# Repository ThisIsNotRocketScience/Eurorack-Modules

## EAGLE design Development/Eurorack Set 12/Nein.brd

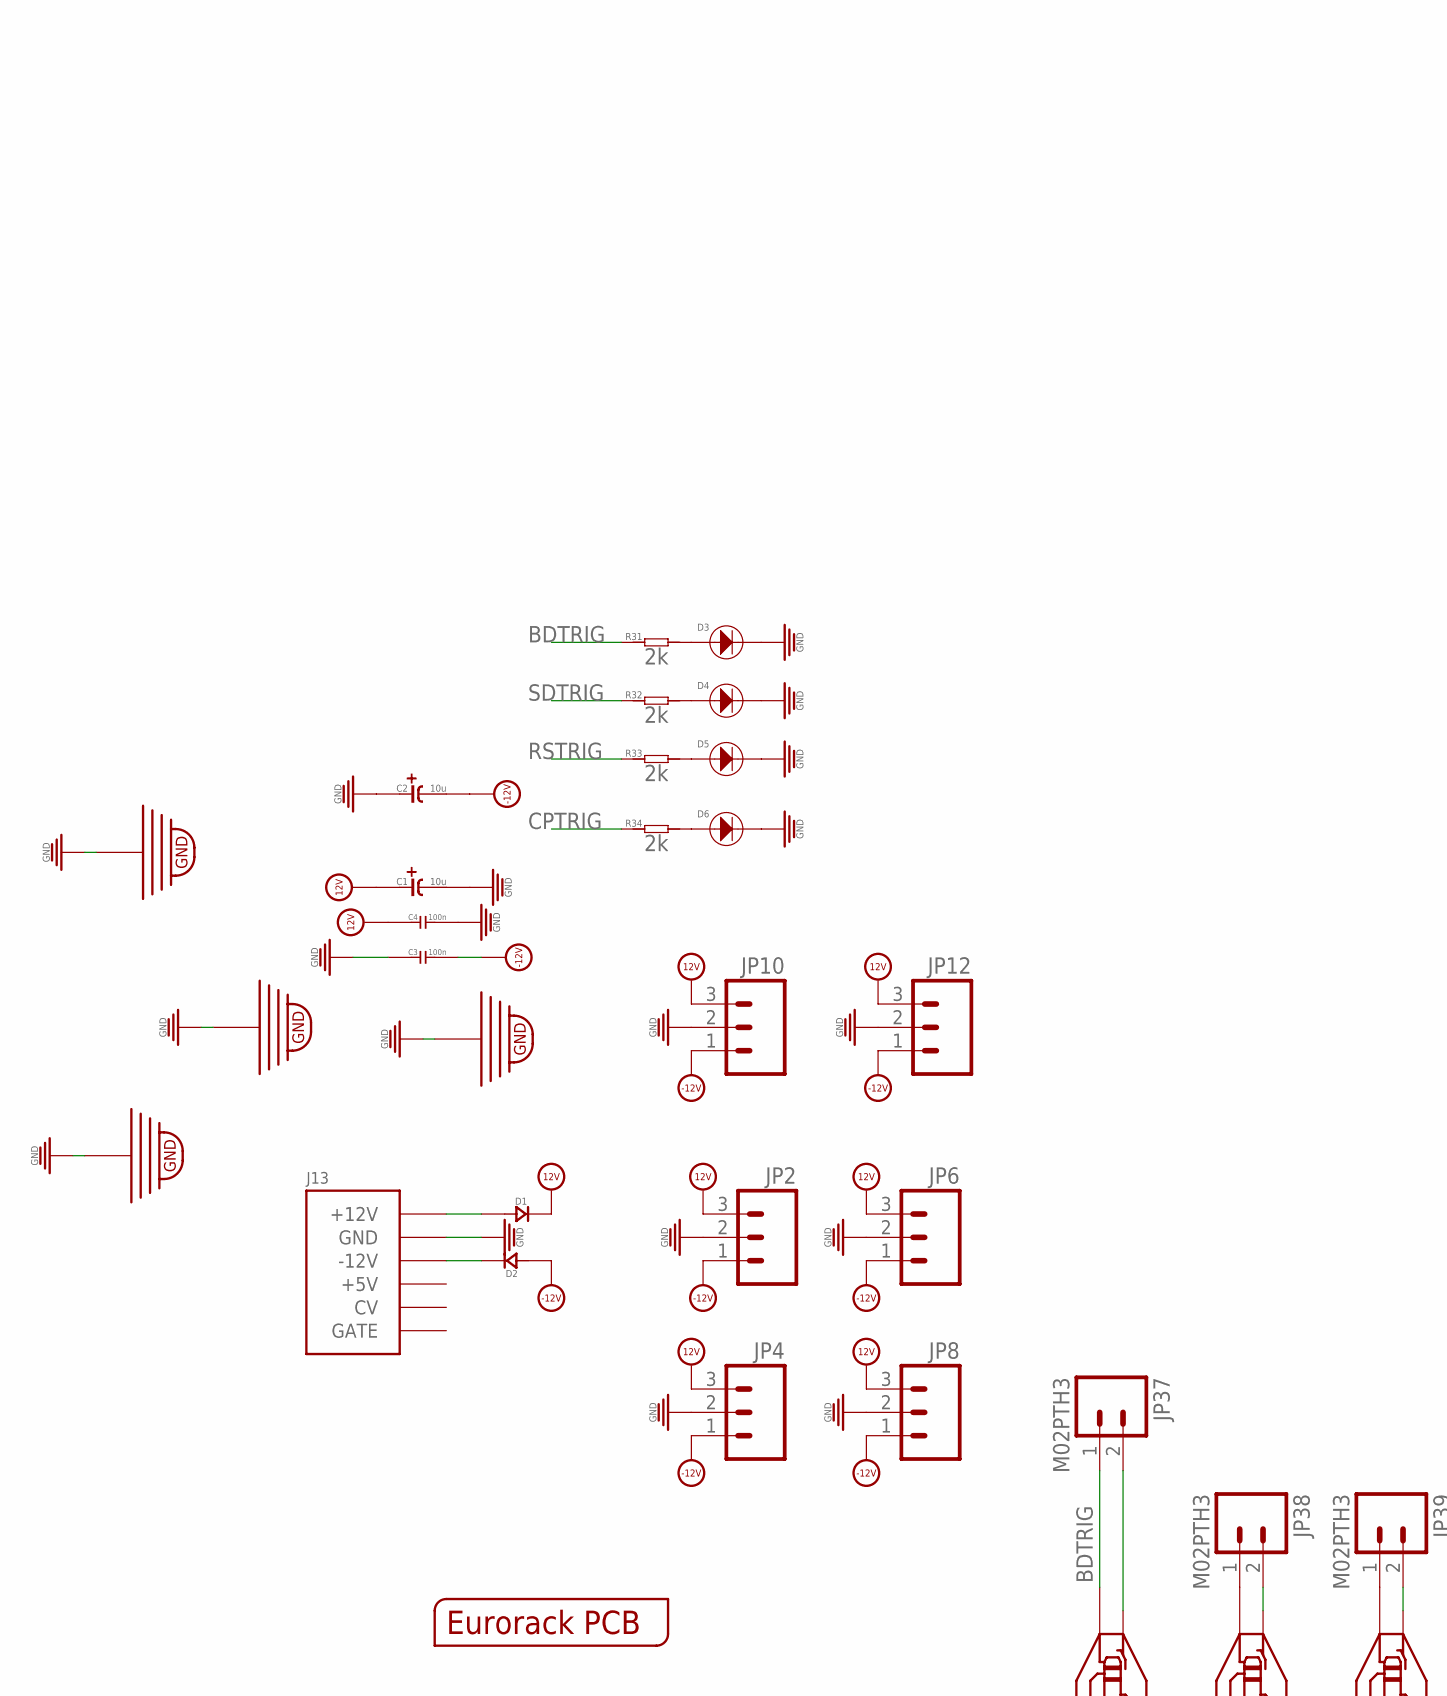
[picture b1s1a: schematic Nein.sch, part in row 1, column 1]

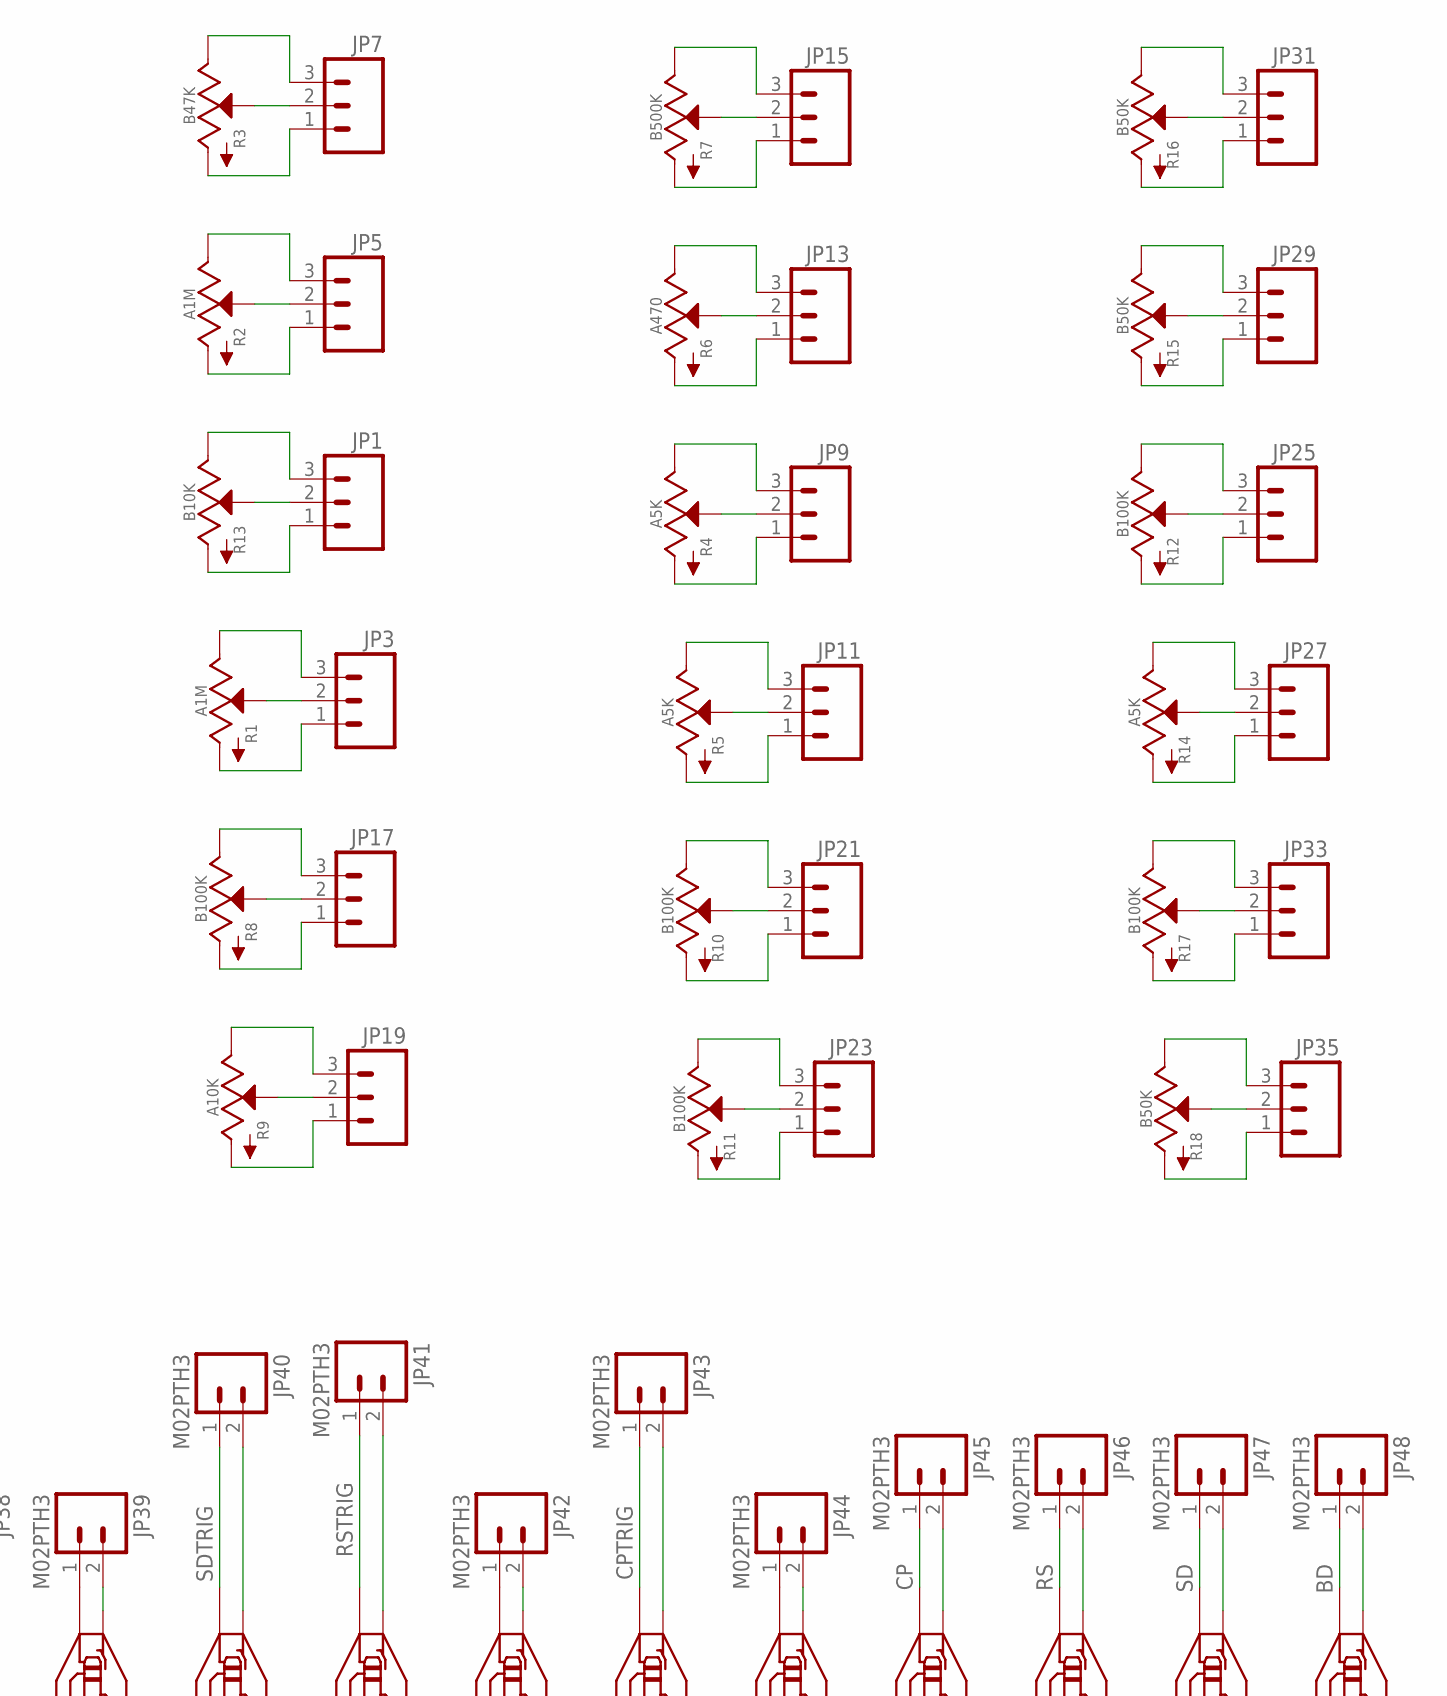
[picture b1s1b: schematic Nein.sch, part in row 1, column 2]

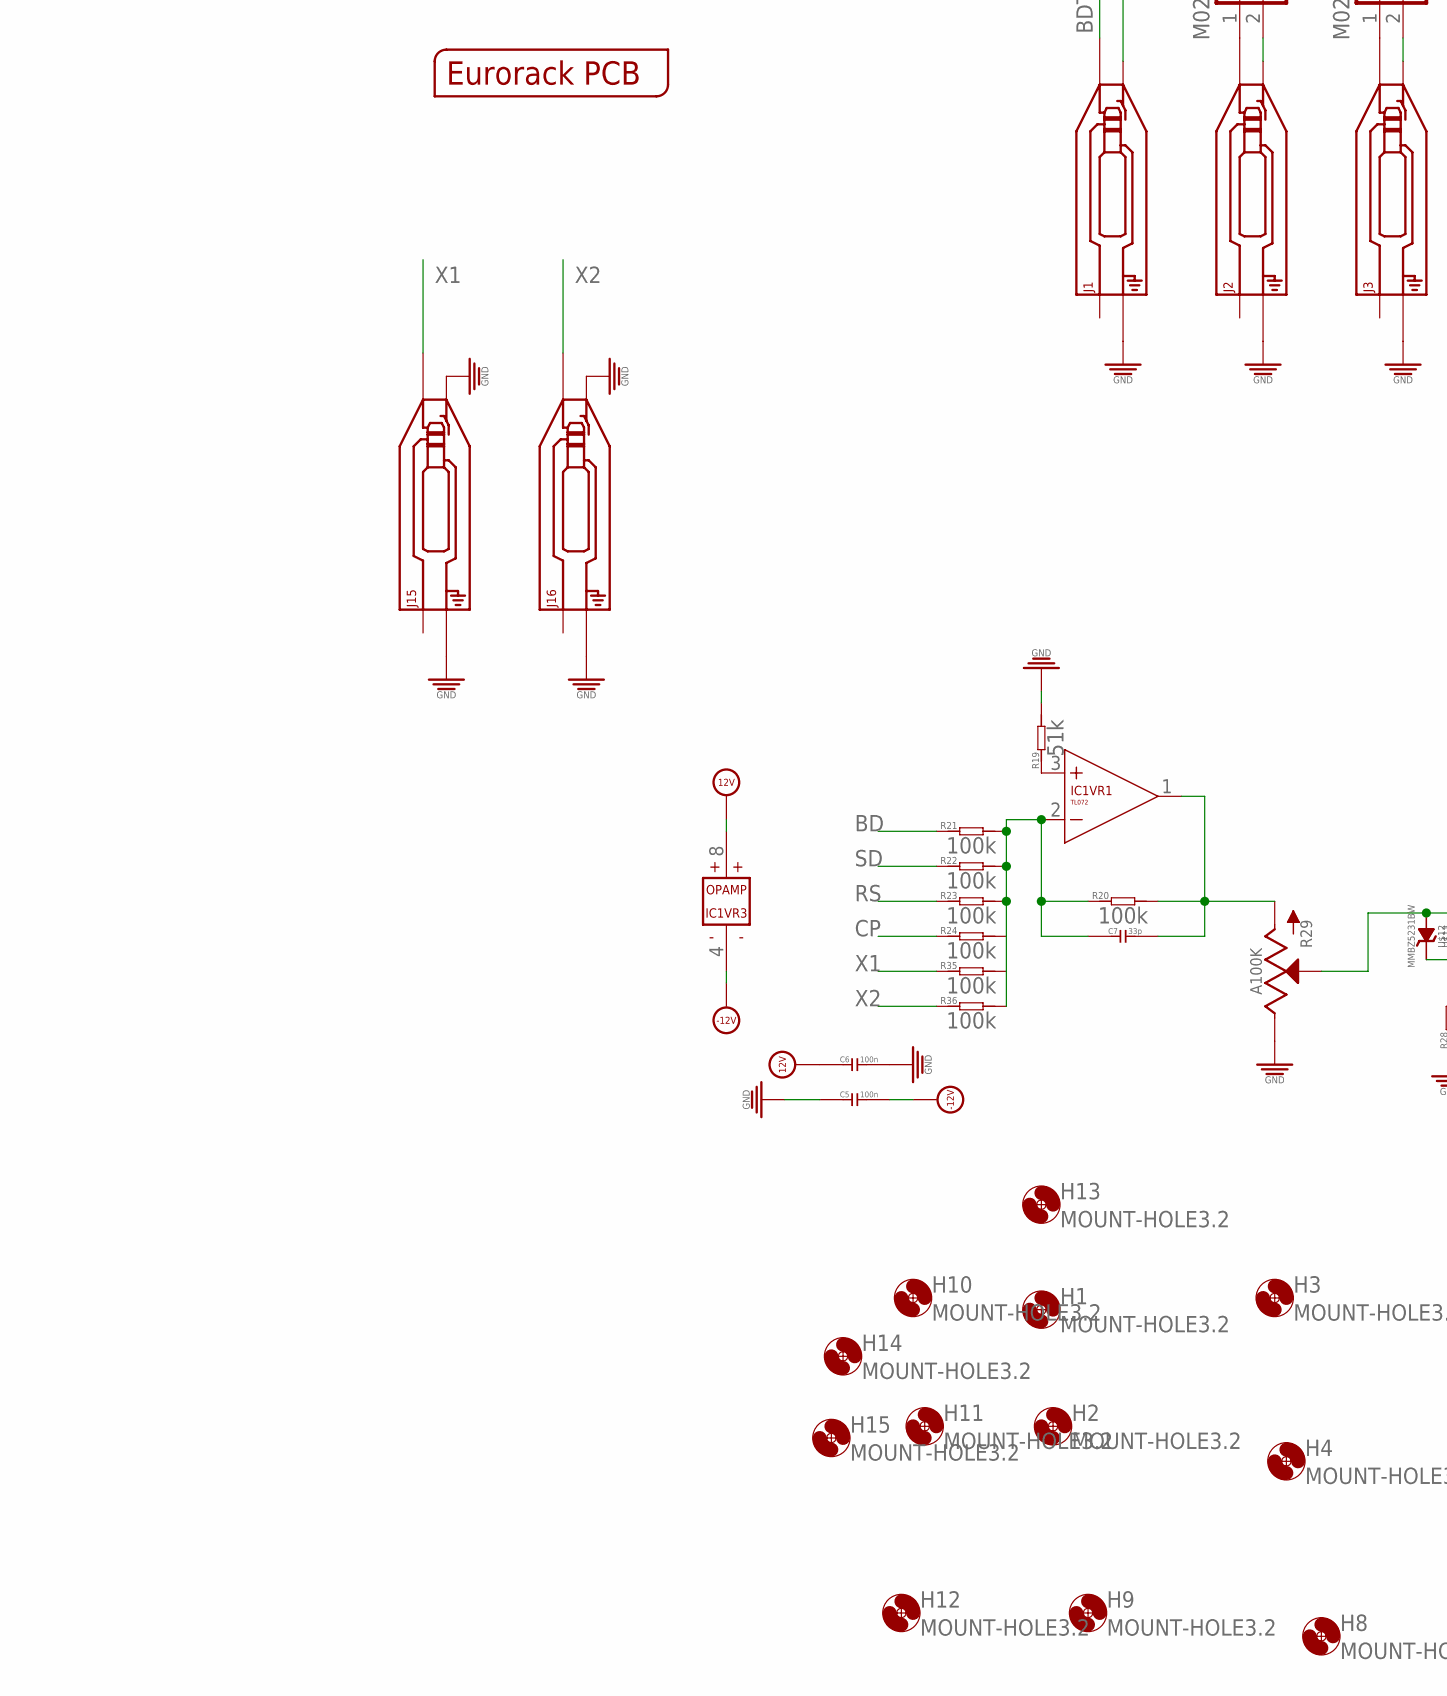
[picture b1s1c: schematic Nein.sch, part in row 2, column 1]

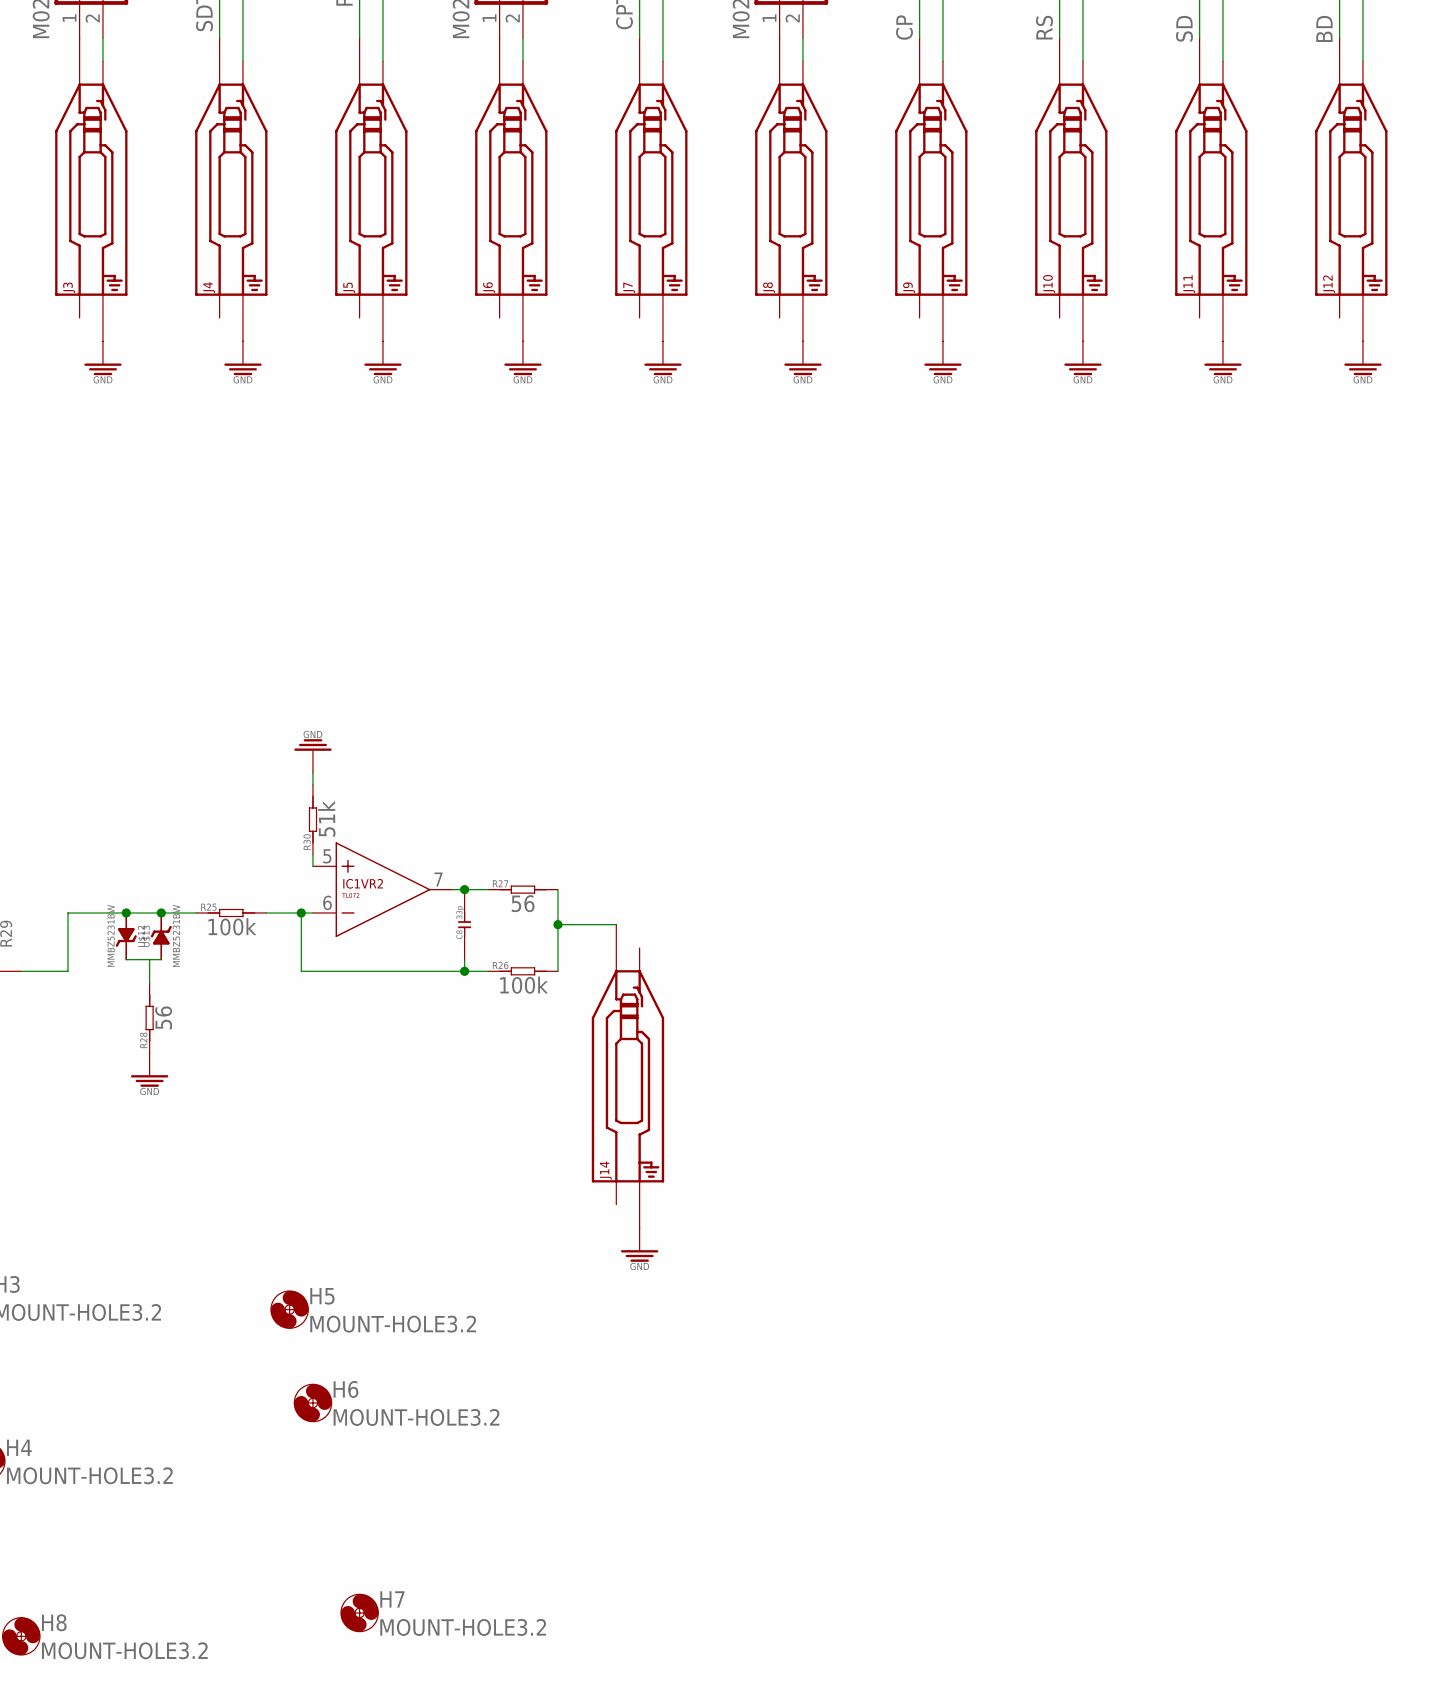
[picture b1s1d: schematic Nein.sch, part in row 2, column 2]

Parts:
C1, C2: 10u; CASE-A_3216
C3, C4, C5, C6: 100n; C0603
C7, C8: 33p; C0603
D1, D2: D-SMA; DO-214AC
D3, D4, D5, D6: LED3MM; 3MMLED
H1, H2, H3, H4, H5, H6, H7, H8, H9, H10, H11, H12, H13, H14, H15: MOUNT-HOLE3.2; 3,2
IC1: TL072; SO08
J1, J2, J3, J4, J5, J6, J7, J8, J9, J10, J11, J12, J14, J15, J16: AUDIO-JACK_SMALLSYMBOLNODRILL; 3.5MM-JACK-SWITCH-13MM-NOHOLES
J13: POWERSHROUDED; POWER_16_SHROUDED
JP1, JP2, JP3, JP4, JP5, JP6, JP7, JP8, JP9, JP10, JP11, JP12, JP13, JP15, JP17, JP19, JP21, JP23, JP25, JP27, JP29, JP31, JP33, JP35: M03LONGPADS; 1X03_LONGPADS
JP37, JP38, JP39, JP40, JP41, JP42, JP43, JP44, JP45, JP46, JP47, JP48: M02PTH3; 1X02_LONGPADS
PCB1: EURORACK_PCB36HP_10CM; EURORACK36HP
R1, R2: A1M; ALPS_POT_SQUAREHOLES
R3: B47K; ALPS_POT_SQUAREHOLES
R4, R5, R14: A5K; ALPS_POT_SQUAREHOLES
R6: A470; ALPS_POT_SQUAREHOLES
R7: B500K; ALPS_POT_SQUAREHOLES
R8, R10, R11, R12, R17: B100K; ALPS_POT_SQUAREHOLES
R9: A10K; ALPS_POT_SQUAREHOLES
R13: B10K; ALPS_POT_SQUAREHOLES
R15, R16, R18: B50K; ALPS_POT_SQUAREHOLES
R19, R30: 51k; R0603
R20, R21, R22, R23, R24, R25, R26, R35, R36: 100k; R0603
R27, R28: 56; R0603
R29: A100K; ALPS_POT_SQUAREHOLES
R31, R32, R33, R34: 2k; R0603
U$4, U$26, U$27, U$28: GNDLOOP; GROUNDLOOP
U$12, U$13: MMBZ5231BW; SOT-323-ZENER

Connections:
12V: C1.+ (1), C4.1, C6.1, D1.2 (-), IC1.8 (V+), JP2.3, JP4.3, JP6.3, JP8.3, JP10.3, JP12.3
-12V: C2.- (2), C3.2, C5.2, D2.1 (+), IC1.4 (V-), JP2.1, JP4.1, JP6.1, JP8.1, JP10.1, JP12.1
BD: J12.TIP_B@1 (TIP), J12.TIP_T@3 (TIP), JP48.1, R21.1
BDTRIG: J1.TIP_B@1 (TIP), J1.TIP_T@3 (TIP), JP37.1, R31.1
CP: J9.TIP_B@1 (TIP), J9.TIP_T@3 (TIP), JP45.1, R24.1
CPTRIG: J7.TIP_B@1 (TIP), J7.TIP_T@3 (TIP), JP43.1, R34.1
GND: C1.- (2), C2.+ (1), C3.1, C4.2, C5.1, C6.2, D3.-, D4.-, D5.-, D6.-, J1.RING_B@1 (RING), J1.RING_T@3 (RING), J2.RING_B@1 (RING), J2.RING_T@3 (RING), J3.RING_B@1 (RING), J3.RING_T@3 (RING), J4.RING_B@1 (RING), J4.RING_T@3 (RING), J5.RING_B@1 (RING), J5.RING_T@3 (RING), J6.RING_B@1 (RING), J6.RING_T@3 (RING), J7.RING_B@1 (RING), J7.RING_T@3 (RING), J8.RING_B@1 (RING), J8.RING_T@3 (RING), J9.RING_B@1 (RING), J9.RING_T@3 (RING), J10.RING_B@1 (RING), J10.RING_T@3 (RING), J11.RING_B@1 (RING), J11.RING_T@3 (RING), J12.RING_B@1 (RING), J12.RING_T@3 (RING), J13.3 (GND), J13.4 (GND), J13.5 (GND), J13.6 (GND), J13.7 (GND), J13.8 (GND), J14.RING_B@1 (RING), J14.RING_T@3 (RING), J15.RING_B@1 (RING), J15.RING_T@3 (RING), J15.SWITCH_B@1 (SWITCH), J15.SWITCH_T@3 (SWITCH), J16.RING_B@1 (RING), J16.RING_T@3 (RING), J16.SWITCH_B@1 (SWITCH), J16.SWITCH_T@3 (SWITCH), JP2.2, JP4.2, JP6.2, JP8.2, JP10.2, JP12.2, R19.2, R28.1, R29.P$1 (E), R30.2, U$4.P$1, U$4.P$2, U$26.P$1, U$26.P$2, U$27.P$1, U$27.P$2, U$28.P$1, U$28.P$2
unnamed: D1.1 (+), J13.9 (+12V), J13.10 (+12V)
unnamed: D2.2 (-), J13.1 (-12V), J13.2 (-12V)
unnamed: JP1.2, R13.P$2 (S)
unnamed: JP1.3, R13.P$1 (E)
unnamed: JP1.1, R13.P$3 (A)
unnamed: JP3.2, R1.P$2 (S)
unnamed: JP3.3, R1.P$1 (E)
unnamed: JP3.1, R1.P$3 (A)
unnamed: JP5.2, R2.P$2 (S)
unnamed: JP5.3, R2.P$1 (E)
unnamed: JP5.1, R2.P$3 (A)
unnamed: JP7.2, R3.P$2 (S)
unnamed: JP7.3, R3.P$1 (E)
unnamed: JP7.1, R3.P$3 (A)
unnamed: JP9.2, R4.P$2 (S)
unnamed: JP9.3, R4.P$1 (E)
unnamed: JP9.1, R4.P$3 (A)
unnamed: JP11.2, R5.P$2 (S)
unnamed: JP11.3, R5.P$1 (E)
unnamed: JP11.1, R5.P$3 (A)
unnamed: JP13.2, R6.P$2 (S)
unnamed: JP13.3, R6.P$1 (E)
unnamed: JP13.1, R6.P$3 (A)
unnamed: JP15.2, R7.P$2 (S)
unnamed: JP15.3, R7.P$1 (E)
unnamed: JP15.1, R7.P$3 (A)
unnamed: JP17.2, R8.P$2 (S)
unnamed: JP17.3, R8.P$1 (E)
unnamed: JP17.1, R8.P$3 (A)
unnamed: JP19.2, R9.P$2 (S)
unnamed: JP19.3, R9.P$1 (E)
unnamed: JP19.1, R9.P$3 (A)
unnamed: JP21.2, R10.P$2 (S)
unnamed: JP21.3, R10.P$1 (E)
unnamed: JP21.1, R10.P$3 (A)
unnamed: JP23.2, R11.P$2 (S)
unnamed: JP23.3, R11.P$1 (E)
unnamed: JP23.1, R11.P$3 (A)
unnamed: JP25.2, R12.P$2 (S)
unnamed: JP25.3, R12.P$1 (E)
unnamed: JP25.1, R12.P$3 (A)
unnamed: JP27.2, R14.P$2 (S)
unnamed: JP27.3, R14.P$1 (E)
unnamed: JP27.1, R14.P$3 (A)
unnamed: JP29.2, R15.P$2 (S)
unnamed: JP29.3, R15.P$1 (E)
unnamed: JP29.1, R15.P$3 (A)
unnamed: JP31.2, R16.P$2 (S)
unnamed: JP31.3, R16.P$1 (E)
unnamed: JP31.1, R16.P$3 (A)
unnamed: JP33.2, R17.P$2 (S)
unnamed: JP33.3, R17.P$1 (E)
unnamed: JP33.1, R17.P$3 (A)
unnamed: JP35.2, R18.P$2 (S)
unnamed: JP35.3, R18.P$1 (E)
unnamed: JP35.1, R18.P$3 (A)
unnamed: J1.SWITCH_B@1 (SWITCH), J1.SWITCH_T@3 (SWITCH), JP37.2
unnamed: J2.TIP_B@1 (TIP), J2.TIP_T@3 (TIP), JP38.1
unnamed: J2.SWITCH_B@1 (SWITCH), J2.SWITCH_T@3 (SWITCH), JP38.2
unnamed: J3.TIP_B@1 (TIP), J3.TIP_T@3 (TIP), JP39.1
unnamed: J3.SWITCH_B@1 (SWITCH), J3.SWITCH_T@3 (SWITCH), JP39.2
unnamed: J4.SWITCH_B@1 (SWITCH), J4.SWITCH_T@3 (SWITCH), JP40.2
unnamed: J5.SWITCH_B@1 (SWITCH), J5.SWITCH_T@3 (SWITCH), JP41.2
unnamed: J6.TIP_B@1 (TIP), J6.TIP_T@3 (TIP), JP42.1
unnamed: J6.SWITCH_B@1 (SWITCH), J6.SWITCH_T@3 (SWITCH), JP42.2
unnamed: J7.SWITCH_B@1 (SWITCH), J7.SWITCH_T@3 (SWITCH), JP43.2
unnamed: J8.TIP_B@1 (TIP), J8.TIP_T@3 (TIP), JP44.1
unnamed: J8.SWITCH_B@1 (SWITCH), J8.SWITCH_T@3 (SWITCH), JP44.2
unnamed: IC1.3 (+IN), R19.1
unnamed: J9.SWITCH_B@1 (SWITCH), J9.SWITCH_T@3 (SWITCH), JP45.2
unnamed: IC1.5 (+IN), R30.1
unnamed: J10.SWITCH_B@1 (SWITCH), J10.SWITCH_T@3 (SWITCH), JP46.2
unnamed: D3.+, R31.2
unnamed: J11.SWITCH_B@1 (SWITCH), J11.SWITCH_T@3 (SWITCH), JP47.2
unnamed: D4.+, R32.2
unnamed: J12.SWITCH_B@1 (SWITCH), J12.SWITCH_T@3 (SWITCH), JP48.2
unnamed: D5.+, R33.2
unnamed: D6.+, R34.2
unnamed: C7.1, IC1.2 (-IN), R20.1, R21.2, R22.2, R23.2, R24.2, R35.2, R36.2
unnamed: R28.2, U$12.CATHODE, U$13.ANODE
unnamed: C7.2, IC1.1 (OUT), R20.2, R29.P$3 (A)
unnamed: C8.1, IC1.6 (-IN), R25.2, R26.1
unnamed: C8.2, IC1.7 (OUT), R27.1
unnamed: J14.TIP_B@1 (TIP), J14.TIP_T@3 (TIP), R26.2, R27.2
unnamed: R25.1, R29.P$2 (S), U$12.ANODE, U$13.CATHODE
RS: J10.TIP_B@1 (TIP), J10.TIP_T@3 (TIP), JP46.1, R23.1
RSTRIG: J5.TIP_B@1 (TIP), J5.TIP_T@3 (TIP), JP41.1, R33.1
SD: J11.TIP_B@1 (TIP), J11.TIP_T@3 (TIP), JP47.1, R22.1
SDTRIG: J4.TIP_B@1 (TIP), J4.TIP_T@3 (TIP), JP40.1, R32.1
X1: J15.TIP_B@1 (TIP), J15.TIP_T@3 (TIP), R35.1
X2: J16.TIP_B@1 (TIP), J16.TIP_T@3 (TIP), R36.1

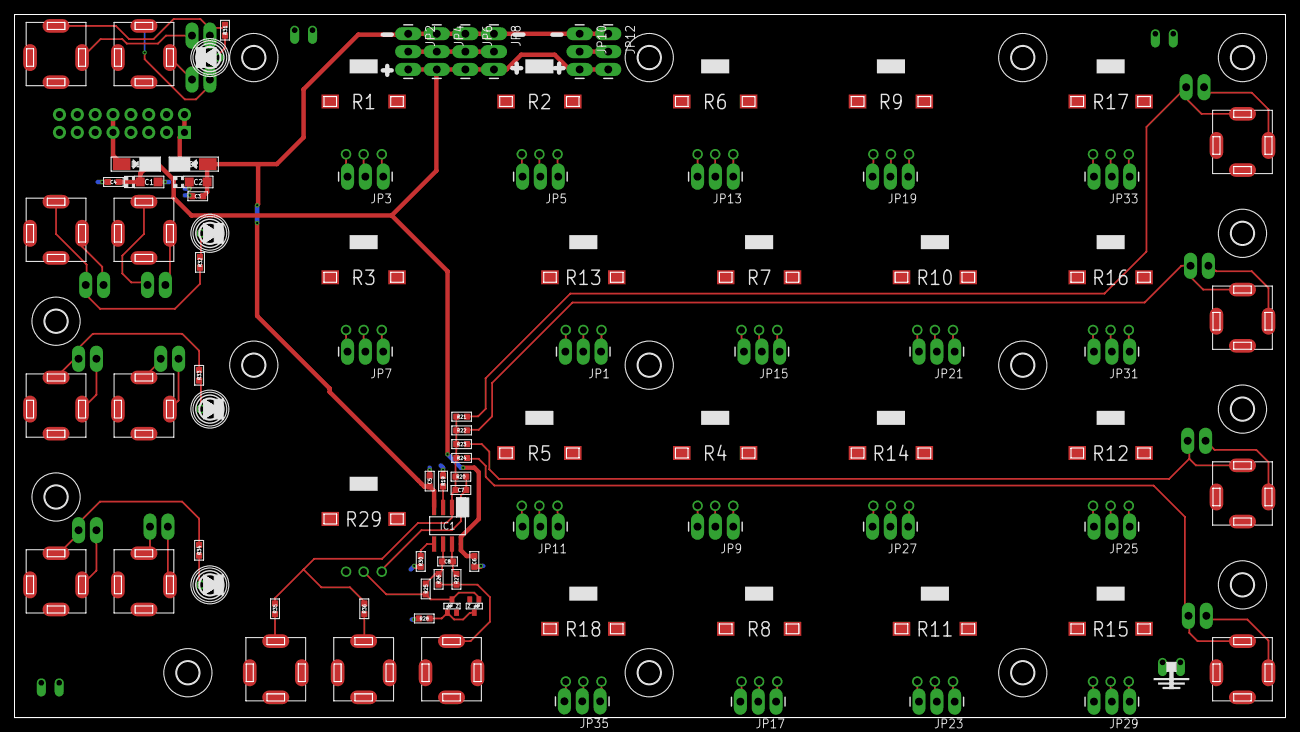
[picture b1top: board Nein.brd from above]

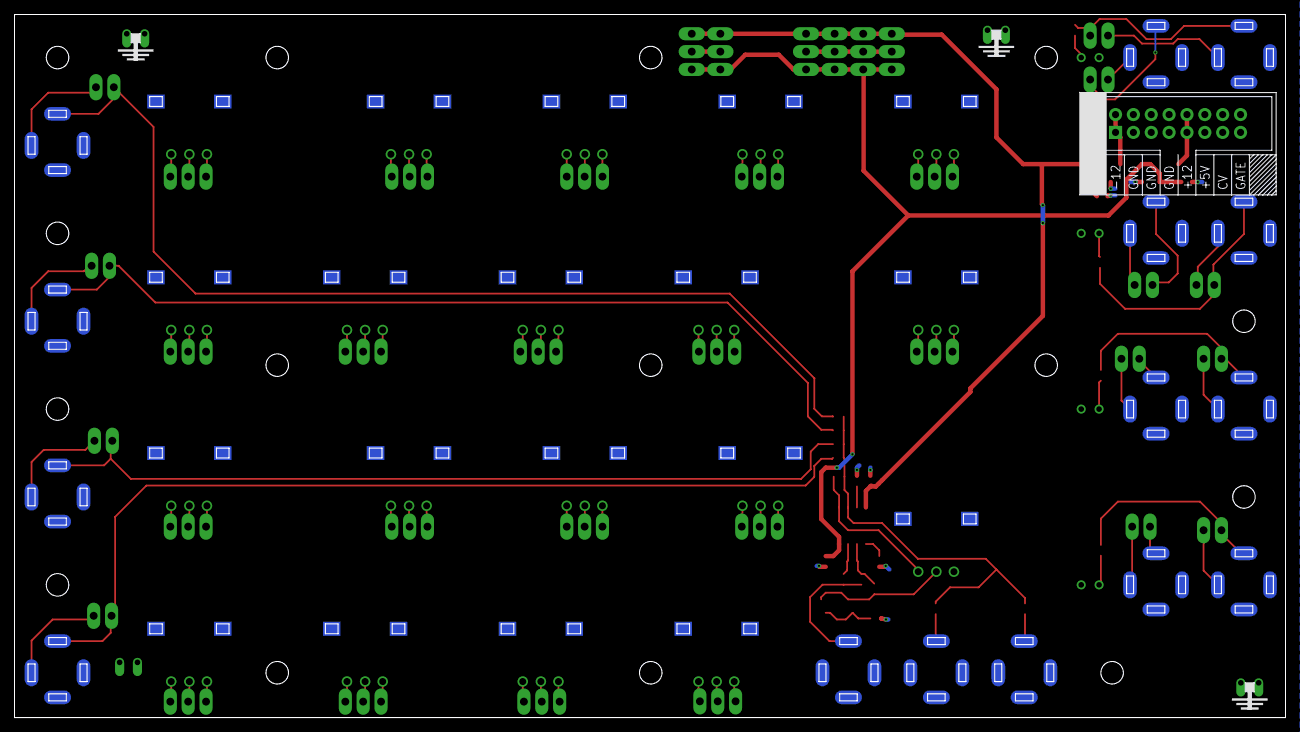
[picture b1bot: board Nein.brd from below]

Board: 2 copper layers, 180.8 x 100.0 mm, 125 parts (4 on the bottom side), 98 nets.

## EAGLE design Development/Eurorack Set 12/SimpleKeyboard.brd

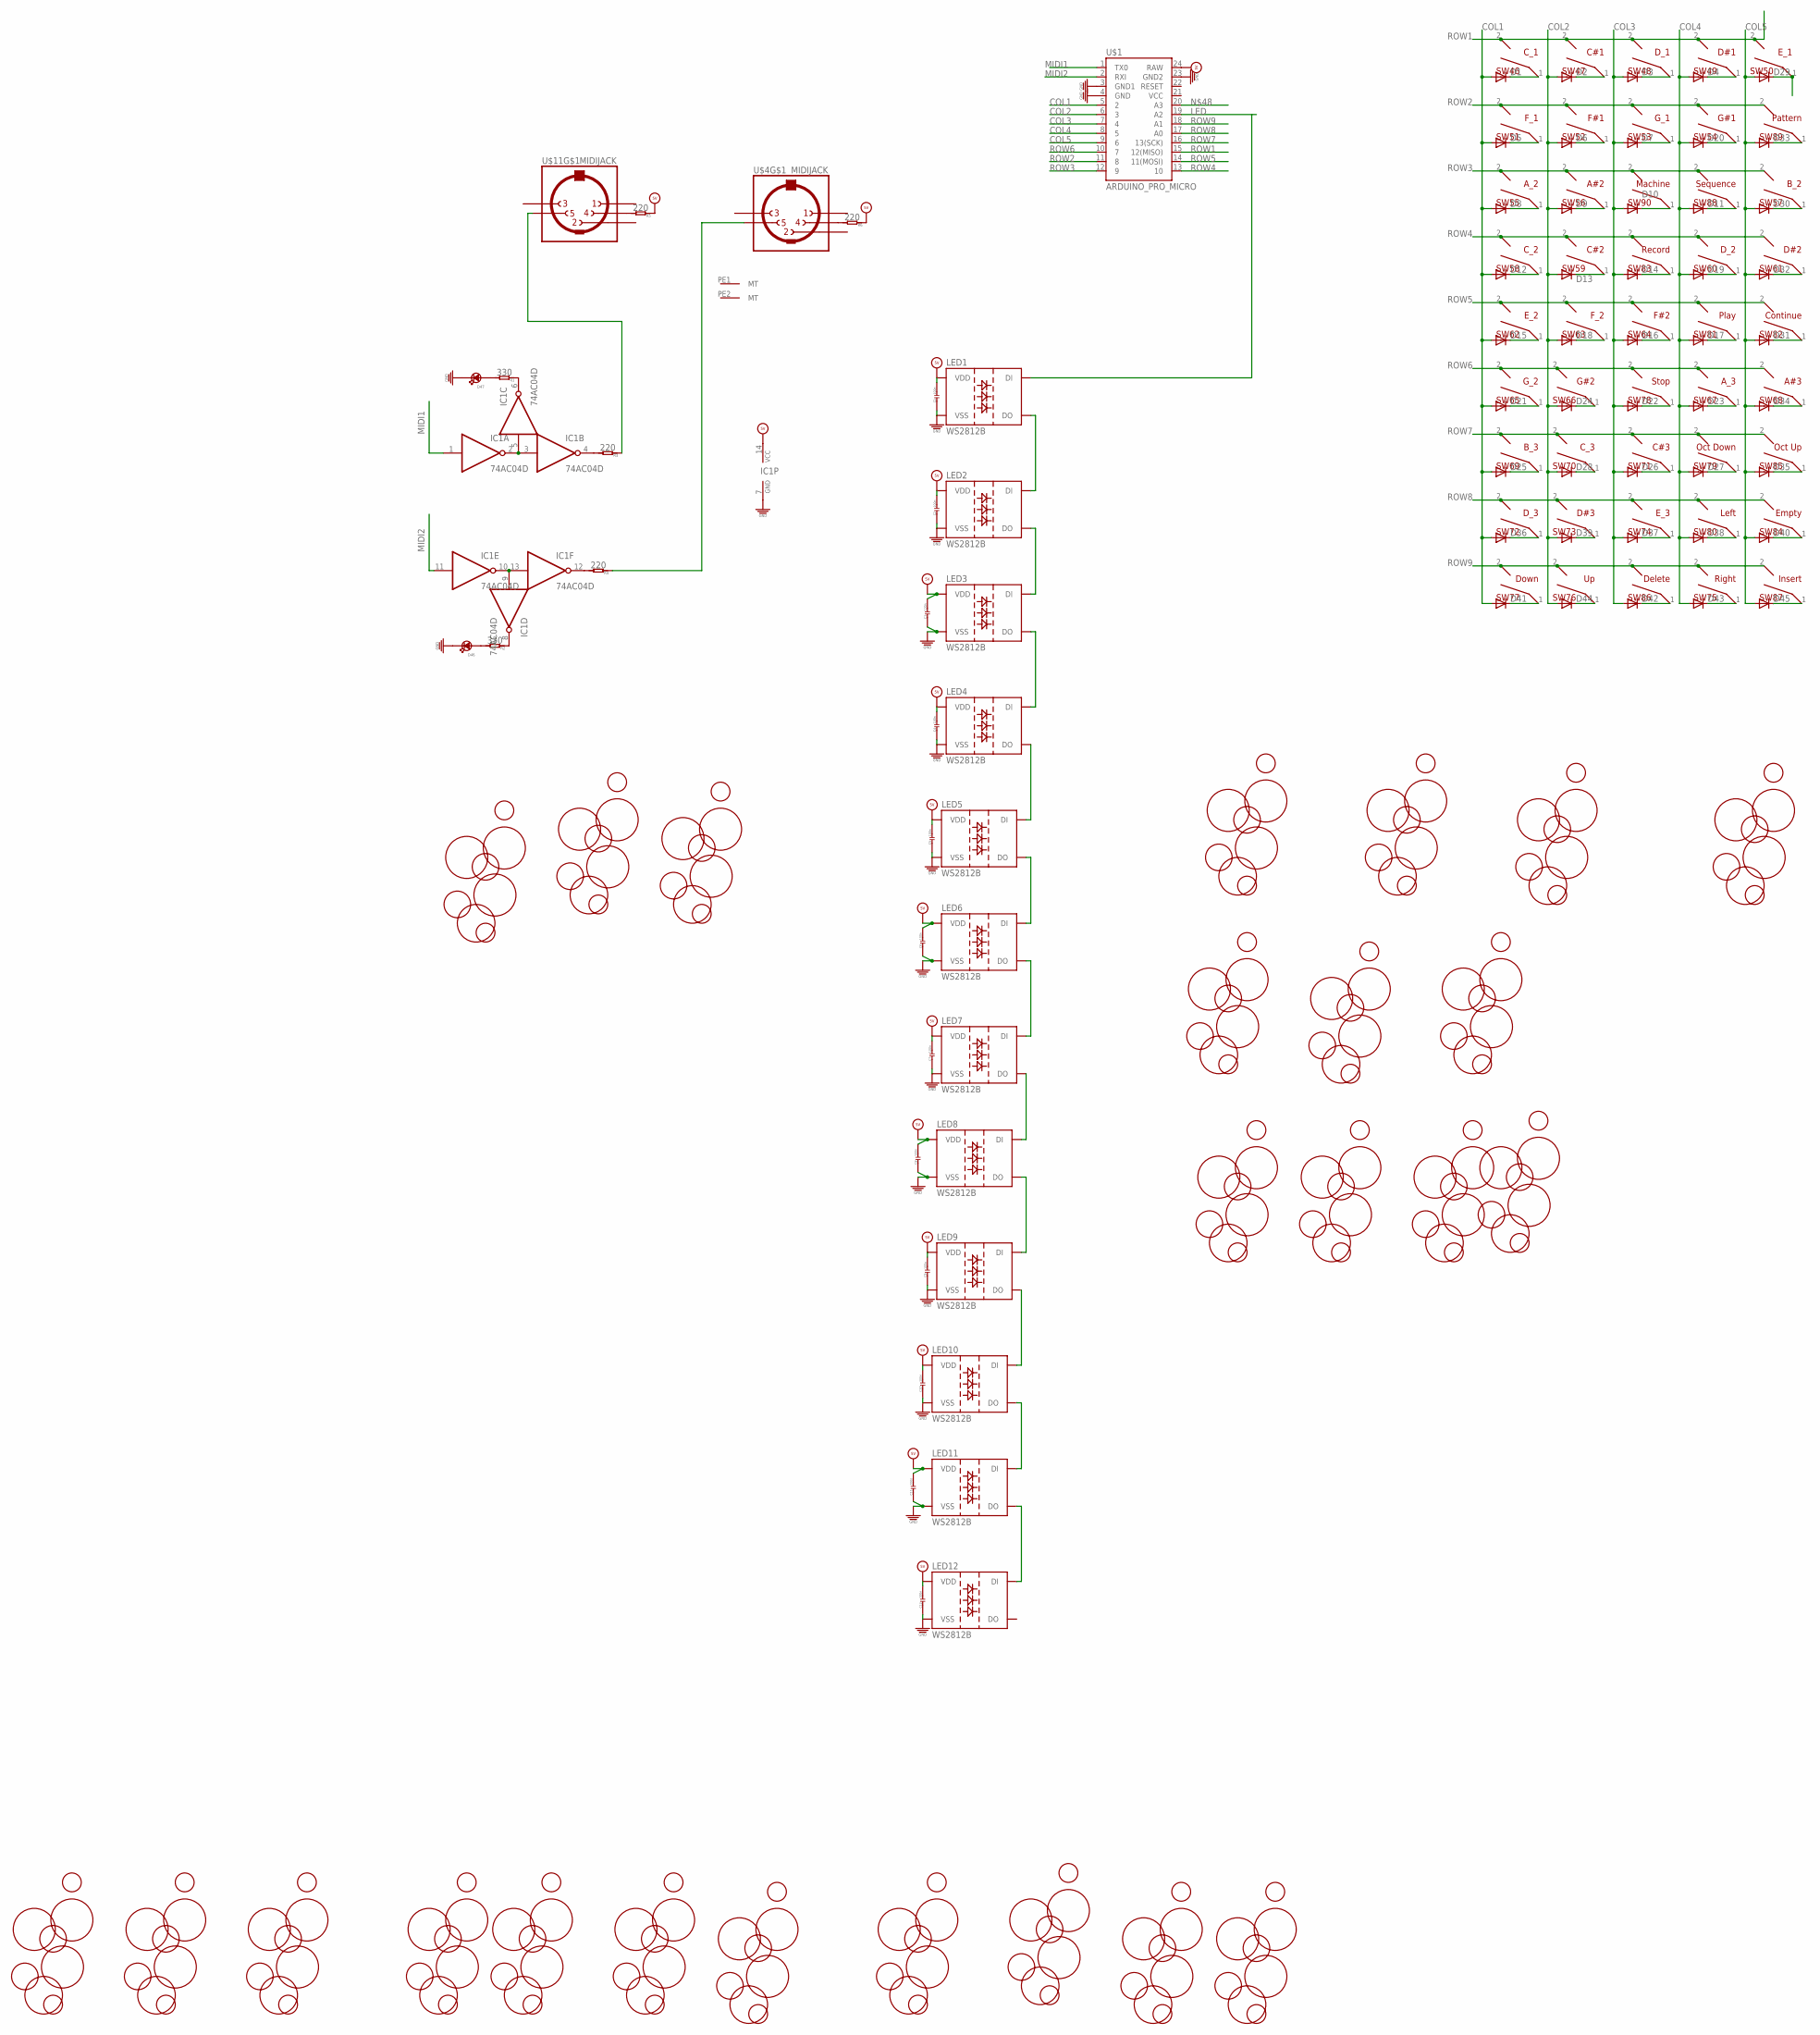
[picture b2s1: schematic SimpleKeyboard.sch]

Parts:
C1, C2, C3, C4, C5, C6, C7, C8, C9, C10, C11, C12: 100n; C0603
D1, D2, D3, D4, D5, D6, D7, D8, D9, D10, D11, D12, D13, D14, D15, D16, D17, D18, D19, D20, D21, D22, D23, D24, D25, D26, D27, D28, D29, D30, D31, D32, D33, D34, D35, D36, D37, D38, D39, D40, D41, D42, D43, D44, D45: CGRM4001-G; SOD-123_MINI-SMA
D46, D47: LED3MM; 3MMLED
IC1: 74AC04D; SO14
LED1, LED2, LED3, LED4, LED5, LED6, LED7, LED8, LED9, LED10, LED11, LED12: WS2812B
R1, R2: 330; R0603
R3, R4, R5, R6: 220; R0603
SW46: C_1; MX1A-XXNW
SW47: C#1; MX1A-XXNW
SW48: D_1; MX1A-XXNW
SW49: D#1; MX1A-XXNW
SW50: E_1; MX1A-XXNW
SW51: F_1; MX1A-XXNW
SW52: F#1; MX1A-XXNW
SW53: G_1; MX1A-XXNW
SW54: G#1; MX1A-XXNW
SW55: A_2; MX1A-XXNW
SW56: A#2; MX1A-XXNW
SW57: B_2; MX1A-XXNW
SW58: C_2; MX1A-XXNW
SW59: C#2; MX1A-XXNW
SW60: D_2; MX1A-XXNW
SW61: D#2; MX1A-XXNW
SW62: E_2; MX1A-XXNW
SW63: F_2; MX1A-XXNW
SW64: F#2; MX1A-XXNW
SW65: G_2; MX1A-XXNW
SW66: G#2; MX1A-XXNW
SW67: A_3; MX1A-XXNW
SW68: A#3; MX1A-XXNW
SW69: B_3; MX1A-XXNW
SW70: C_3; MX1A-XXNW
SW71: C#3; MX1A-XXNW
SW72: D_3; MX1A-XXNW
SW73: D#3; MX1A-XXNW
SW74: E_3; MX1A-XXNW
SW75: Right; MX1A-XXNW
SW76: Up; MX1A-XXNW
SW77: Down; MX1A-XXNW
SW78: Stop; MX1A-XXNW
SW79: Oct Down; MX1A-XXNW
SW80: Left; MX1A-XXNW
SW81: Play; MX1A-XXNW
SW82: Continue; MX1A-XXNW
SW83: Record; MX1A-XXNW
SW84: Empty; MX1A-XXNW
SW85: Oct Up; MX1A-XXNW
SW86: Delete; MX1A-XXNW
SW87: Insert; MX1A-XXNW
SW88: Sequence; MX1A-XXNW
SW89: Pattern; MX1A-XXNW
SW90: Machine; MX1A-XXNW
U$1: ARDUINO_PRO_MICRO
U$4, U$11: MIDIJACK; CP-2350
U$15, U$16, U$17, U$18, U$19, U$20: BUBBLESDSA_1U; BUBBLES
U$21, U$22, U$33: BUBBLESDSA_1U_HALF; BUBBLES_HALF
U$28, U$29, U$30, U$31, U$32: BUBBLESINV; BUBBLES_INV
U$34, U$35, U$36, U$37, U$38, U$39, U$40, U$41, U$42, U$43, U$44: BUBBLESONE; BUBBLES_ONE

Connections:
5V: C1.2, C2.2, C3.2, C4.2, C5.2, C6.2, C7.2, C8.2, C9.2, C10.2, C11.2, C12.2, IC1.14 (VCC), LED1.VDD, LED2.VDD, LED3.VDD, LED4.VDD, LED5.VDD, LED6.VDD, LED7.VDD, LED8.VDD, LED9.VDD, LED10.VDD, LED11.VDD, LED12.VDD, R5.1, R6.1, U$1.24 (RAW)
COL1: D1.A, D5.A, D8.A, D12.A, D15.A, D21.A, D25.A, D36.A, D41.A, U$1.5 (2)
COL2: D2.A, D6.A, D9.A, D13.A, D18.A, D24.A, D28.A, D39.A, D44.A, U$1.6 (3)
COL3: D3.A, D7.A, D10.A, D14.A, D16.A, D22.A, D26.A, D37.A, D42.A, U$1.7 (4)
COL4: D4.A, D11.A, D17.A, D19.A, D20.A, D23.A, D27.A, D38.A, D43.A, U$1.8 (5)
COL5: D29.A, D30.A, D31.A, D32.A, D33.A, D34.A, D35.A, D40.A, D45.A, U$1.9 (6)
GND: C1.1, C2.1, C3.1, C4.1, C5.1, C6.1, C7.1, C8.1, C9.1, C10.1, C11.1, C12.1, D46.-, D47.-, IC1.7 (GND), LED1.VSS, LED2.VSS, LED3.VSS, LED4.VSS, LED5.VSS, LED6.VSS, LED7.VSS, LED8.VSS, LED9.VSS, LED10.VSS, LED11.VSS, LED12.VSS, U$1.3 (GND1), U$1.4 (GND), U$1.23 (GND2)
LED: LED1.DIN (DI), U$1.19 (A2)
MIDI1: IC1.1 (I), U$1.1 (TX0)
MIDI2: IC1.11 (I), U$1.2 (RXI)
unnamed: D1.C, SW46.1
unnamed: D2.C, SW47.1
unnamed: D3.C, SW48.1
unnamed: D4.C, SW49.1
unnamed: D5.C, SW51.1
unnamed: D6.C, SW52.1
unnamed: D7.C, SW53.1
unnamed: D8.C, SW55.1
unnamed: D9.C, SW56.1
unnamed: D10.C, SW90.1
unnamed: D11.C, SW88.1
unnamed: D12.C, SW58.1
unnamed: D13.C, SW59.1
unnamed: D14.C, SW83.1
unnamed: D15.C, SW62.1
unnamed: D16.C, SW64.1
unnamed: D17.C, SW81.1
unnamed: D18.C, SW63.1
unnamed: D19.C, SW60.1
unnamed: D20.C, SW54.1
unnamed: D21.C, SW65.1
unnamed: D22.C, SW78.1
unnamed: D23.C, SW67.1
unnamed: D24.C, SW66.1
unnamed: D25.C, SW69.1
unnamed: D26.C, SW71.1
unnamed: D27.C, SW79.1
unnamed: D28.C, SW70.1
unnamed: D29.C, SW50.1
unnamed: D30.C, SW57.1
unnamed: D31.C, SW82.1
unnamed: D32.C, SW61.1
unnamed: D33.C, SW89.1
unnamed: D34.C, SW68.1
unnamed: D35.C, SW85.1
unnamed: D36.C, SW72.1
unnamed: D37.C, SW74.1
unnamed: D38.C, SW80.1
unnamed: D39.C, SW73.1
unnamed: D40.C, SW84.1
unnamed: D41.C, SW77.1
unnamed: D42.C, SW86.1
unnamed: D43.C, SW75.1
unnamed: D44.C, SW76.1
unnamed: D45.C, SW87.1
unnamed: D46.+, R2.2
unnamed: LED3.DOUT (DO), LED4.DIN (DI)
unnamed: LED2.DOUT (DO), LED3.DIN (DI)
unnamed: LED1.DOUT (DO), LED2.DIN (DI)
unnamed: LED8.DOUT (DO), LED9.DIN (DI)
unnamed: LED6.DOUT (DO), LED7.DIN (DI)
unnamed: LED5.DOUT (DO), LED6.DIN (DI)
unnamed: LED4.DOUT (DO), LED5.DIN (DI)
unnamed: IC1.2 (O), IC1.3 (I), IC1.5 (I)
unnamed: IC1.9 (I), IC1.10 (O), IC1.13 (I)
unnamed: IC1.6 (O), R1.1
unnamed: IC1.8 (O), R2.1
unnamed: D47.+, R1.2
unnamed: IC1.4 (O), R3.2
unnamed: IC1.12 (O), R4.2
unnamed: R5.2, U$11.4
unnamed: R6.2, U$4.4
unnamed: R3.1, U$11.5
unnamed: R4.1, U$4.5
unnamed: LED7.DOUT (DO), LED8.DIN (DI)
unnamed: LED11.DOUT (DO), LED12.DIN (DI)
unnamed: LED10.DOUT (DO), LED11.DIN (DI)
unnamed: LED9.DOUT (DO), LED10.DIN (DI)
ROW1: SW46.2, SW47.2, SW48.2, SW49.2, SW50.2, U$1.15 (12(MISO))
ROW2: SW51.2, SW52.2, SW53.2, SW54.2, SW89.2, U$1.11 (8)
ROW3: SW55.2, SW56.2, SW57.2, SW88.2, SW90.2, U$1.12 (9)
ROW4: SW58.2, SW59.2, SW60.2, SW61.2, SW83.2, U$1.13 (10)
ROW5: SW62.2, SW63.2, SW64.2, SW81.2, SW82.2, U$1.14 (11(MOSI))
ROW6: SW65.2, SW66.2, SW67.2, SW68.2, SW78.2, U$1.10 (7)
ROW7: SW69.2, SW70.2, SW71.2, SW79.2, SW85.2, U$1.16 (13(SCK))
ROW8: SW72.2, SW73.2, SW74.2, SW80.2, SW84.2, U$1.17 (A0)
ROW9: SW75.2, SW76.2, SW77.2, SW86.2, SW87.2, U$1.18 (A1)

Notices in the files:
parts and their libraries:
SparkFun-Connectors: Licensing: CC v3.0 Share-Alike You are welcome to use this library for commercial purposes.
